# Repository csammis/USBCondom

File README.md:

# USB Condom

A board to allow my iPhone to charge while decoupling the USB data lines to prevent juice jacking. 2017 is strange times.

Designed in KiCad.

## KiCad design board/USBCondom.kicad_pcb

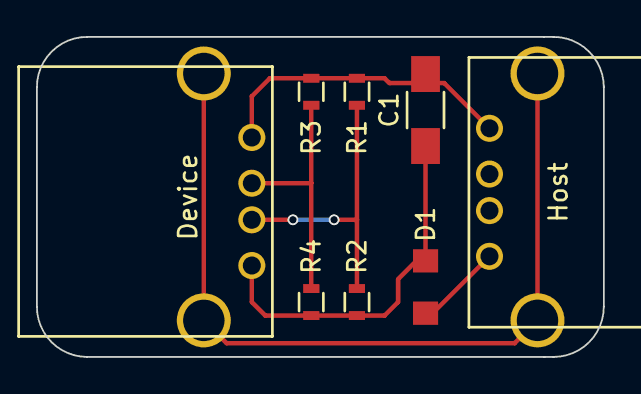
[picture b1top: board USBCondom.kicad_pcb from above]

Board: 2 copper layers, 31.5 x 17.8 mm, 6 parts (0 on the bottom side), 4 nets.

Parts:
C1: 100uF; C_1206_HandSoldering
D1: SR206; DO-219AB
R1: 75K; R_0603
R2, R4: 49.9K; R_0603
R3: 59K; R_0603

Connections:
/D+: R1.2, R2.1
/D-: R3.2, R4.1
/GND: C1.2, R1.1, R3.1
/VCCphone: C1.1, D1.1, R2.2, R4.2

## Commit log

2017-10-15 Update board to rev 2
    Bugfixes:
    * USB shields are no longer connected to GND
    Updates:
    * Changed C1 footprint to 1206_HandSoldering for larger pads
    * Shrank down board size and made layout more compact
2017-10-22 Update board to rev 3
    Bugfixes:
    * USB device side no longer has Vcc and GND swapped
    Updates:
    * Rounded corners on PCB
    * Extended PBC to give host side port more support
